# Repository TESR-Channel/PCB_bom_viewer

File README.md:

<p align="center">
  
</p>

<h1 align="center">TESR BOM Viewer <sub>v1.50</sub></h1>
<p align="center"><b>จากถุงอะไหล่ → ตำแหน่งบนบอร์ด</b> · From the bag to the board</p>

<p align="center">
  <a href="https://tesr-channel.github.io/PCB_bom_viewer/"><b>▶ เปิดใช้งานบนเว็บ / Open the web app</b></a> ·
  <a href="https://tesr-channel.github.io/PCB_bom_viewer/?demo=1">ตัวอย่าง KiCad</a> ·
  <a href="https://tesr-channel.github.io/PCB_bom_viewer/?demo=jlc">ตัวอย่างไฟล์ JLCPCB</a> ·
  <a href="https://www.tesrshop.com">tesrshop.com</a>
</p>

---

เครื่องมือช่วยประกอบ PCB ด้วยมือ — เปิดไฟล์ KiCad แล้ว **สแกนฉลากถุงอะไหล่ (LCSC / DigiKey / Mouser) ด้วยเว็บแคมหรือกล้องมือถือ** โปรแกรมจะไฮไลต์ว่าชิ้นนั้นต้องวางตรงไหนบนบอร์ดทันที หรือจะ **พิมพ์รหัสเอง** / **คลิกแถวในตาราง** / **คลิกชิ้นส่วนบนภาพบอร์ด 2D หรือ 3D** ก็ได้ทุกทาง

ทำงานในเบราว์เซอร์ 100% — ไม่มีเซิร์ฟเวอร์ ไม่ส่งไฟล์หรือภาพจากกล้องขึ้นคลาวด์

## ความสามารถ

| | |
|---|---|
| 📂 **เปิดไฟล์** | `.kicad_pcb` (KiCad 6 / 7 / 8 / 9) ลากวางได้เลย · เติม LCSC / MPN จาก BOM `.csv` (JLCPCB / KiCad) · หรือใช้ BOM + CPL `.csv` อย่างเดียวก็ได้ |
| 📷 **สแกน** | QR (LCSC / JLCPCB), DataMatrix ECIA (DigiKey / Mouser / Arrow), Code128 / 1D (`1P…`, `P…`) ผ่านเว็บแคม กล้องมือถือ หรือรูปถ่าย |
| ⌨️ **พิมพ์ / ยิงบาร์โค้ด** | พิมพ์ LCSC (`C8734`), MPN, Ref (`R25`), Value (`10k`) · รองรับเครื่องยิงบาร์โค้ด USB โดยไม่ต้องคลิกช่อง |
| 🖱️ **คลิกเลือก** | ตาราง BOM ↔ บอร์ด 2D (บน / ล่าง / สองด้าน) ↔ บอร์ด 3D (หมุน ซูม คลิกชิ้นส่วน) ซิงค์กันทั้งหมด |
| 🗂️ **ดูเลเยอร์** | แถบแท็บเลเยอร์แบบ **Altium Designer** ใต้ภาพบอร์ด (Top Layer · Bottom Layer · Mechanical 1 · Top/Bottom Overlay · Paste · Solder …), ปุ่ม LS, Single Layer Mode `Shift+S`, `+` `−` `*` เปลี่ยนเลเยอร์, `Q` mm/mil · แผงเลเยอร์ (กด `L`): เปิด/ปิด ทองแดงบน/ล่าง/ชั้นใน, ซิลค์สกรีน, โซลเดอร์มาสก์, Paste, Fab, Courtyard, Edge.Cuts, รูเจาะ, เลเยอร์ผู้ใช้ · โหมด **สมจริง** / **สีเลเยอร์ (CAD)** · ชุดมุมมอง ด้านบน / ด้านล่าง / ทองแดง / กลไก ฯลฯ · ดับเบิลคลิกดูเลเยอร์เดียว · High contrast · ใช้กับ 2D และ 3D |
| 📱 **ทุกอุปกรณ์** | ตรวจอุปกรณ์อัตโนมัติ: คอมพิวเตอร์ (3 คอลัมน์) · iPad / แท็บเล็ต (บอร์ด + แท็บ BOM / สแกน) · มือถือ (เมนูล่าง บอร์ด / BOM / สแกน) · รองรับแนวตั้ง/แนวนอน · จอสัมผัส: สองนิ้วซูม แตะสองครั้งพอดีจอ · เปลี่ยนเองได้ในตั้งค่า |
| ✅ **เช็กลิสต์** | ติ๊ก "หยิบแล้ว" / "วางแล้ว" รายชิ้น · แถบความคืบหน้า · บันทึกอัตโนมัติในเครื่อง · Export `.csv` |
| 🎨 **ธีม TESR** | ดำ / แดงเข้ม / ทอง · ภาษาไทย / English · PCB สีดำ / เขียว / ขาว |

## ต้องใช้ไฟล์อะไร?

กด **เปิดไฟล์** ในเว็บ จะมีหน้าต่างบอกให้ใส่ทีละช่อง — เลือกทางใดทางหนึ่ง

**A. ไฟล์ KiCad (ง่ายสุด)**

| ไฟล์ | ใช้ทำอะไร | |
|---|---|---|
| `.kicad_pcb` | ตาราง BOM + บอร์ด 2D + 3D ครบในไฟล์เดียว | จำเป็น |
| BOM `.csv` / `.xlsx` | เติมเลข LCSC / MPN (ถ้าไม่ได้ใส่ไว้ใน KiCad) เพื่อให้สแกนถุงเจอ | เสริม |

**B. ไฟล์สั่ง PCB + PCBA ของ JLCPCB** (ชุดเดียวกับที่อัปโหลดสั่งงาน — ใช้ได้กับ KiCad / EasyEDA / Altium)

| ไฟล์ | ใช้ทำอะไร | |
|---|---|---|
| **BOM** `.csv` / `.xlsx` | รายการชิ้นส่วน (Comment, Designator, Footprint, LCSC) → ตาราง + สแกนถุง | จำเป็น |
| **CPL** (Pick & Place) `.csv` / `.xlsx` | ตำแหน่งชิ้นส่วน (Designator, Mid X, Mid Y, Layer, Rotation) → ไฮไลต์บนบอร์ด | แนะนำ |
| **Gerber** `.zip` | รูปร่างบอร์ด pad รู silkscreen → ภาพ 2D / 3D เหมือนจริง | แนะนำ |

| ไฟล์ที่มี | ตาราง BOM | สแกนถุง | 2D | 3D |
|---|---|---|---|---|
| `.kicad_pcb` | ✓ | ✓* | ✓ | ✓ |
| BOM | ✓ | ✓ | — | — |
| BOM + CPL | ✓ | ✓ | กล่องตามตำแหน่ง | กล่องตามตำแหน่ง |
| BOM + CPL + Gerber | ✓ | ✓ | ✓ | ✓ |

\* สแกนถุงต้องมีเลข LCSC หรือ MPN ใน BOM · ตำแหน่ง CPL จะถูกจัดให้ตรงกับ Gerber อัตโนมัติ

**หาไฟล์จากไหน** — KiCad: *File → Fabrication Outputs → Gerbers + Drill* (zip รวม), BOM/CPL จากปลั๊กอิน *Fabrication Toolkit* · EasyEDA: *Fabrication → PCB Fabrication File / BOM / Pick and Place File* · Altium: *Gerber + NC Drill / Bill of Materials / Pick and Place*

## วิธีใช้

1. เปิด **https://tesr-channel.github.io/PCB_bom_viewer/** (Chrome / Edge / Safari — มือถือก็ได้)
2. กด **เปิดไฟล์** แล้วใส่ไฟล์ตามช่อง (หรือลากไฟล์ทั้งหมดมาวาง ระบบแยกประเภทให้เอง)
3. กด **เปิดกล้อง** แล้วส่องฉลากถุง → ชิ้นที่ต้องวางจะกะพริบสีแดงบนบอร์ด
4. วางเสร็จ คลิก Ref (เช่น `R25`) ในกล่อง "รายการที่เลือก" หรือคลิกชิ้นนั้นบนบอร์ดอีกครั้ง เพื่อติ๊กว่าวางแล้ว

**คีย์ลัด**: `↑ / ↓` เลือกแถว · `Space` วางชิ้นถัดไปของแถว · `/` ไปช่องรหัส · `L` แผงเลเยอร์ · `Shift+S` Single Layer · `+` `−` `*` เปลี่ยนเลเยอร์ · `Q` mm/mil · `Esc` ยกเลิกเลือก

> กล้องต้องใช้ HTTPS หรือ `localhost` — บน GitHub Pages ใช้ได้ทันที
> ใช้งานแบบออฟไลน์: ดาวน์โหลด repo แล้วรัน `python3 -m http.server` ในโฟลเดอร์ จากนั้นเปิด `http://localhost:8000`

## เวอร์ชัน

เลขเวอร์ชันแสดงที่มุมบนซ้าย (กดเพื่อดู "มีอะไรใหม่") และท้ายหน้า · ประวัติทั้งหมดอยู่ใน [CHANGELOG.md](CHANGELOG.md) · แก้เลขเวอร์ชันที่ `js/version.js` · ก่อน deploy ทุกครั้งรัน `tools/set-build.sh <tag>` เพื่อให้เบราว์เซอร์โหลดไฟล์ใหม่ทั้งหมด (กัน cache เก่าปนกัน)

## English

**TESR BOM Viewer** is a browser-only assembly helper for KiCad boards. Load a `.kicad_pcb` — or the JLCPCB order set (BOM + CPL + Gerber .zip, any EDA) — then scan a part bag (LCSC QR, DigiKey / Mouser ECIA DataMatrix, 1D barcodes) with a webcam or phone, type an LCSC / MPN / reference / value, or click a BOM row or a part in the 2D / 3D view — the matching parts are highlighted everywhere. Sourced / placed state is saved locally per board and can be exported as CSV. Nothing is uploaded; all decoding runs locally (ZXing C++ compiled to WebAssembly).

## Project layout

```
index.html          app shell
css/style.css       TESR theme
js/app.js           state, table, selection, scanning, settings
js/kicad.js         .kicad_pcb parser, BOM grouping, CSV BOM / CPL import
js/gerber.js        Gerber RS-274X + Excellon reader, BOM + CPL + Gerber board builder
js/xlsx.js          minimal .xlsx reader
js/version.js       version number + change log
js/scan.js          label parsing (LCSC / ECIA / 1D), matching, camera + decoder
js/view2d.js        2D canvas board view
js/view3d.js        3D board view (three.js)
js/device.js        device detection (phone / tablet / computer) + layout choice
js/layers.js        PCB layer model: layer list, colours, stacking order, presets
js/paint.js         board painter: realistic look, technical overlays, CAD layer colours
vendor/             three.js r169, zxing-wasm 2.2.4, fflate 0.8.2 (bundled for offline use)
demo/               TESR Pincer V2: KiCad board + BOM, and demo/jlcpcb/ BOM + CPL + Gerber
```

## Third-party

- [three.js](https://threejs.org) — MIT
- [fflate](https://github.com/101arrowz/fflate) — MIT
- [zxing-wasm](https://github.com/Sec-ant/zxing-wasm) / [zxing-cpp](https://github.com/zxing-cpp/zxing-cpp) — MIT / Apache-2.0
- Fonts: Chakra Petch, IBM Plex Sans Thai, IBM Plex Mono — SIL Open Font License
- Inspired by the idea behind the *Bag BOM* KiCad plugin (scan a bag, see where it goes)

---

<p align="center">Made by <a href="https://www.tesrshop.com"><b>TESR</b></a> — Thai Embedded System and Robotics</p>

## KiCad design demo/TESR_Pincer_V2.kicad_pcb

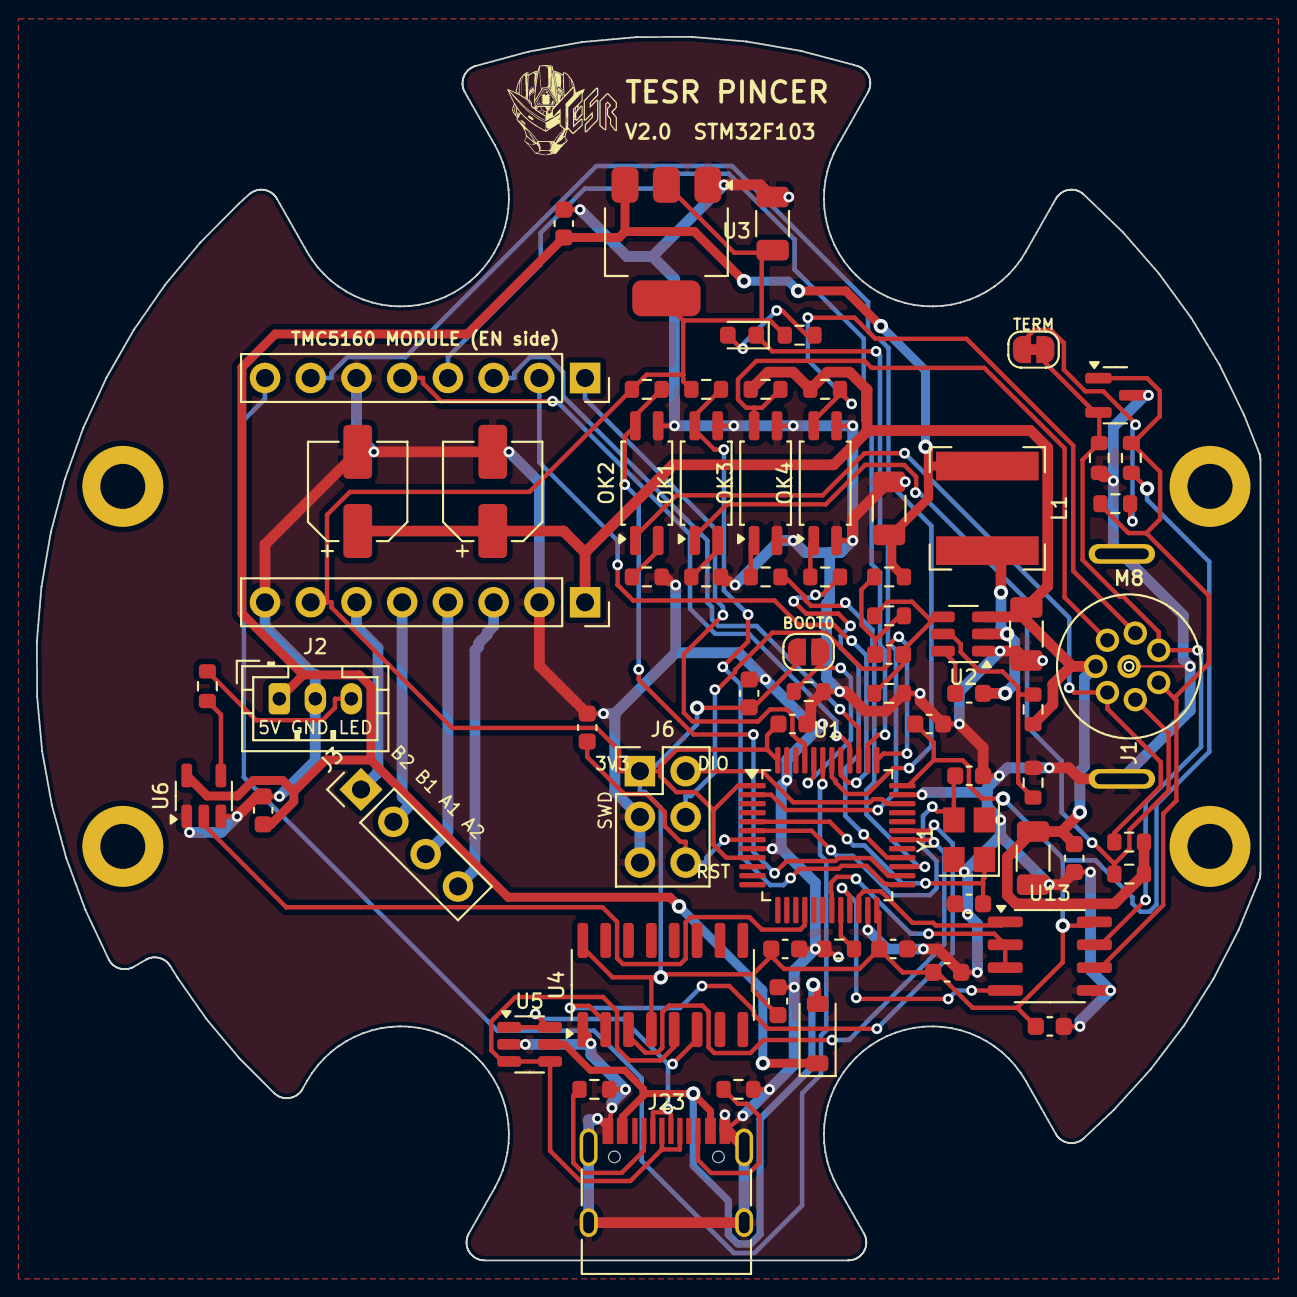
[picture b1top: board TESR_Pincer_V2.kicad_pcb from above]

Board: 2 copper layers, 68.0 x 68.0 mm, 77 parts (1 on the bottom side), 57 nets.

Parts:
C2, C12, C17, C18, C19, C20, C24, C27, C28: 100nF; C_0603_1608Metric
C3, C16: 22uF 25V; C_1206_3216Metric
C7, C14: 22uF 35V; CP_Elec_5x5.8
C8: 75pF; C_0603_1608Metric
C9: 100nF 50V; C_0603_1608Metric
C10, C11: 10uF 50V; C_1206_3216Metric
C15: 10uF; C_0603_1608Metric
C21: 1uF; C_0603_1608Metric
C23: 4.7uF; C_0603_1608Metric
C25, C26: 20pF; C_0603_1608Metric
D1: B5819W; D_SOD-123
D2: STATUS (green); LED_0603_1608Metric
D33: SM712-02HTG; SOT-23
H1, H2, H3, H4: M2.5; MountingHole_2.5mm_Pad4.5
J1: M8 8P; M8_8P_PCB
J2: LED (5V GND DIN); JST_PH_B3B-PH-K_1x03_P2.00mm_Vertical
J3: Motor (B2 B1 A1 A2); PinHeader_1x04_P2.54mm_Vertical
J4: TMC5160 logic; PinSocket_1x08_P2.54mm_Vertical
J5: TMC5160 power; PinSocket_1x08_P2.54mm_Vertical
J6: SWD; PinHeader_2x03_P2.54mm_Vertical
J23: USB-C 16P; USB_C_Receptacle_HRO_TYPE-C-31-M-12
JP1: BOOT0; SolderJumper-2_P1.3mm_Open_RoundedPad1.0x1.5mm
JP2: TERM; SolderJumper-2_P1.3mm_Bridged_RoundedPad1.0x1.5mm
L1: 10uH 3A; L_Bourns-SRN6028
LOGO1: TESR_Logo_5mm
LOGO2: TESR_Logo_10mm
OK1, OK2, OK3, OK4: LTV-214-G; SOP-4_4.4x2.6mm_P1.27mm
R2: 100k; R_0603_1608Metric
R3: 49.9R; R_0603_1608Metric
R4: 13.3k; R_0603_1608Metric
R5, R6, R8, R10, R15, R16, R24, R25: 10k; R_0603_1608Metric
R7, R9: 2k; R_0603_1608Metric
R11, R13: 220R; R_0603_1608Metric
R12, R14: 3.9k; R_0603_1608Metric
R20, R21, R73, R74: 5.1k; R_0603_1608Metric
R22: 33R; R_0603_1608Metric
R26: 1k; R_0603_1608Metric
R72: 120R; R_0603_1608Metric
U1: STM32F103C8T6; LQFP-48_7x7mm_P0.5mm
U2: TPS54302DDCR; SOT-23-6
U3: AMS1117-3.3; SOT-223-3_TabPin2
U4: CH340C; SOIC-16_3.9x9.9mm_P1.27mm
U5: USBLC6-2SC6; SOT-23-6
U6: 74AHCT1G125; SOT-23-5
U13: SP3485EN; SOIC-8_3.9x4.9mm_P1.27mm
Y1: 8MHz; Crystal_SMD_3225-4Pin_3.2x2.5mm

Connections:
+3V3: C12.1, C16.1, C17.1, C18.1, C19.1, C20.1, C21.1, C23.1, C27.1, J5.7, J6.1, JP1.1, R8.1, R10.1, R26.1, R73.1, U1.1, U1.9, U1.24, U1.36, U1.48, U3.2, U4.4, U4.16, U13.8
+5V: C3.1, C15.1, C28.1, D1.1, J2.1, L1.2, R3.1, U3.3, U6.5
+24V: C7.1, C9.1, C10.1, C11.1, C14.1, J1.5, J5.1, R5.1, R12.1, R14.1, R15.1, R16.1, U2.3
BOOT0: JP1.2, R24.1, U1.44
BOOT1: R25.1, U1.20
BUCK_BOOT: C2.1, U2.6
BUCK_EN: R5.2, R6.1, U2.5
BUCK_FB: C8.2, R2.2, R4.1, U2.4
BUCK_FBX: C8.1, R2.1, R3.2
DRV_CS: J4.4, U1.38
DRV_DIR: J4.8, U1.43
DRV_EN: J4.1, U1.45
DRV_STEP: J4.7, U1.42
GND: C3.2, C7.2, C9.2, C10.2, C11.2, C12.2, C14.2, C15.2, C16.2, C17.2, C18.2, C19.2, C20.2, C21.2, C23.2, C24.2, C25.2, C26.2, C27.2, C28.2, D33.3, J1.8, J1.MP, J2.2, J4.6, J5.2, J5.8, J6.3, J6.5, J23.A1, J23.A12, J23.B1, J23.B12, J23.S1, OK1.3, OK2.3, OK3.2, OK3.3, OK4.2, OK4.3, R4.2, R6.2, R7.2, R9.2, R20.2, R21.2, R24.2, R25.2, R74.2, U1.8, U1.23, U1.35, U1.47, U2.1, U3.1, U4.1, U5.2, U6.1, U6.3, U13.5, Y1.2, Y1.4
IN1: J1.7, OK1.1, R16.2
IN1_3V3: OK1.4, R8.2, U1.25
IN1_K: OK1.2, R7.1
IN2: J1.6, OK2.1, R15.2
IN2_3V3: OK2.4, R10.2, U1.26
IN2_K: OK2.2, R9.1
LED_BUF: R22.1, U6.4
LED_DATA: J2.3, R22.2
LED_DIN: U1.16, U6.2
LED_STAT: D2.1, U1.2
LED_STAT_A: D2.2, R26.2
MOT_A1: J3.3, J5.4
MOT_A2: J3.4, J5.3
MOT_B1: J3.2, J5.5
MOT_B2: J3.1, J5.6
NRST: C24.1, J6.6, U1.7
OSC_IN: C25.1, U1.5, Y1.1
OSC_OUT: C26.1, U1.6, Y1.3
OUT1: J1.4, OK3.4, R12.2
OUT1_3V3: R11.1, U1.27
OUT1_LED: OK3.1, R11.2
OUT2: J1.3, OK4.4, R14.2
OUT2_3V3: R13.1, U1.28
OUT2_LED: OK4.1, R13.2
RS485_A: D33.1, J1.1, R72.1, R73.2, U13.6
RS485_B: D33.2, J1.2, JP2.2, R74.1, U13.7
RS485_DE: U1.19, U13.2, U13.3
RS485_DI: U1.21, U13.4
RS485_RO: U1.22, U13.1
RS485_TERM: JP2.1, R72.2
SPI_MISO: J4.5, U1.40
SPI_MOSI: J4.2, U1.41
SPI_SCK: J4.3, U1.39
SW: C2.2, L1.1, U2.2
SWCLK: J6.4, U1.37
SWDIO: J6.2, U1.34
UART1_RX: U1.31, U4.2
UART1_TX: U1.30, U4.3
USB_CC1: J23.A5, R20.1
USB_CC2: J23.B5, R21.1
USB_DN: J23.A7, J23.B7, U4.6, U5.1, U5.6
USB_DP: J23.A6, J23.B6, U4.5, U5.3, U5.4
VBUS: D1.2, J23.A4, J23.A9, J23.B4, J23.B9, U5.5

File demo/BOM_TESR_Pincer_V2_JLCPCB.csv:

Comment,Designator,Footprint,LCSC Part #,MPN / note,Qty
100nF,"C2,C12,C17,C18,C19,C20,C24,C27,C28",C_0603_1608Metric,C14663,,9
22uF 25V,"C3,C16",C_1206_3216Metric,C12891,,2
22uF 35V,"C7,C14",CP_Elec_5x5.8,C23289,,2
75pF,C8,C_0603_1608Metric,C1681,,1
100nF 50V,C9,C_0603_1608Metric,C14663,,1
10uF 50V,"C10,C11",C_1206_3216Metric,C13585,CL31A106KBHNNNE,2
10uF,C15,C_0603_1608Metric,C19702,,1
1uF,C21,C_0603_1608Metric,C15849,,1
4.7uF,C23,C_0603_1608Metric,C19666,,1
20pF,"C25,C26",C_0603_1608Metric,C1648,,2
B5819W,D1,D_SOD-123,C8598,B5819W,1
STATUS (green),D2,LED_0603_1608Metric,C72043,,1
SM712-02HTG,D33,SOT-23,C172881,SM712-02HTG,1
LED (5V GND DIN),J2,JST_PH_B3B-PH-K_1x03_P2.00mm_Vertical,C131339,B3B-PH-K-S(LF)(SN),1
Motor (B2 B1 A1 A2),J3,PinHeader_1x04_P2.54mm_Vertical,C2897367,PM254-1-04-Z-8.5,1
TMC5160 logic,J4,PinSocket_1x08_P2.54mm_Vertical,C27438,2.54mm 1x8P female header,1
TMC5160 power,J5,PinSocket_1x08_P2.54mm_Vertical,C27438,2.54mm 1x8P female header,1
SWD (1:3V3 2:SWDIO 3:GND 4:SWCLK 5:GND 6:NRST),J6,PinHeader_2x03_P2.54mm_Vertical,C2897404,PM254-2-03-Z-8.5,1
USB-C 16P,J23,USB_C_Receptacle_HRO_TYPE-C-31-M-12,C165948,HRO TYPE-C-31-M-12,1
10uH 3A,L1,L_Bourns-SRN6028,C2827403,SNR6028TYD100M 6x6 10uH (SRN6028-100M equiv.),1
LTV-214-G,"OK1,OK2,OK3,OK4",SOP-4_4.4x2.6mm_P1.27mm,C133122,LTV-214-G,4
100k,R2,R_0603_1608Metric,C25803,,1
49.9R,R3,R_0603_1608Metric,C23185,,1
13.3k,R4,R_0603_1608Metric,C100759,,1
10k,"R5,R6,R8,R10,R15,R16,R24,R25",R_0603_1608Metric,C25804,,8
2k,"R7,R9",R_0603_1608Metric,C22975,,2
220R,"R11,R13",R_0603_1608Metric,C22962,,2
3.9k,"R12,R14",R_0603_1608Metric,C23018,,2
5.1k,"R20,R21,R73,R74",R_0603_1608Metric,C23186,,4
33R,R22,R_0603_1608Metric,C23140,,1
1k,R26,R_0603_1608Metric,C21190,,1
120R,R72,R_0603_1608Metric,C22787,,1
STM32F103C8T6,U1,LQFP-48_7x7mm_P0.5mm,C8734,STM32F103C8T6,1
TPS54302DDCR,U2,SOT-23-6,C311983,TPS54302DDCR,1
AMS1117-3.3,U3,SOT-223-3_TabPin2,C6186,AMS1117-3.3,1
CH340C,U4,SOIC-16_3.9x9.9mm_P1.27mm,C84681,CH340C,1
USBLC6-2SC6,U5,SOT-23-6,C7519,USBLC6-2SC6,1
74AHCT1G125,U6,SOT-23-5,C7484,SN74AHCT1G125DBVR,1
SP3485EN,U13,SOIC-8_3.9x4.9mm_P1.27mm,C8963,SP3485EN-L/TR,1
8MHz,Y1,Crystal_SMD_3225-4Pin_3.2x2.5mm,C9002,X322508MSB4SI,1
